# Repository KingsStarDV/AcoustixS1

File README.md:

My project AcoustixS1 is a fire extinuguisher which unlike other typical extinguisher uses SOUND WAVES to put out a flame.

Using AcoustixS1 is simple-
Turn on the toggle switch and sweep through the different frequencies using the rotary encoder.
The flame will get extinguish as you sweep through the frequencies.

I made this project as this one is unique.
I also wanted to spend my time productively.
This will also act as a line of safety for anyone who makes it.

Here is the wiring diagram-

Here is the BOM (Bill of Material)-

|Sn Number|Name|Qty|Cost|Link|
|---------|----|---|----|----|
|1|Speaker\Driver|1|950|https://www.amazon.in/FABTEC-Bass-Subwoofer-Enhanced-Low-End/dp/B0DT6CSNG8/ref=sr_1_3?crid=192DP10O75A17&dib=eyJ2IjoiMSJ9.OVpzjIeE52x4uN2hVDxxlCX0qLCRxQbtG2erD7AwG6yxwMZ7f8EWv4AVLL8WUgkA_mpQjQT_Fj_pkmhrqkyTCTO5OtNT8bGWQ8LzFvCHTCzksd2-O8yrDJKDanAHCFvzN9EQYej6w1EGBaCOx9iobEC0Yx1TN75c8lDfNnSlfrQBt9jvxze4_mL_LDm_8DIAyUvBkURTbzSwiUdASAhmS_RULj338rKEiICikLi7wDc.RIsxd0z1ZItF1Hz5PVSEdKenKYNS3Z0KPM8KLFPRmJU&dib_tag=se&keywords=fabtech%2Bsubwoofer&qid=1773637421&sprefix=FABTEC%2Caps%2C736&sr=8-3&th=1|
|2|Raspberry Pi Pico|1|390|https://robu.in/product/raspberry-pi-pico/?gad_source=1&gad_campaignid=19974686076&gbraid=0AAAAADvLFWe03Hg1PItPT--gApqtRKEj9&gclid=Cj0KCQjwsdnNBhC4ARIsAA_3hei-cacvVxjyf118IHT753eRSVcyLpk3J3DV5El-KJ_P3qYJ6TD2-goaAsIzEALw_wcB
|3|Toggle Switch|1|50|https://robu.in/product/1-month-warranty-210/?gad_source=1&gad_campaignid=17427802703&gbraid=0AAAAADvLFWcb8t9bmv2to3qo8X2Oi7sTG&gclid=Cj0KCQjwsdnNBhC4ARIsAA_3hehINwRSVwfC4ErZaWfJz_EuXLBkshijYFT9KsB1gMIg2Z3ElRRyuA8aAtuDEALw_wcB
|4|ICL7660|3|16*3|https://www.flyrobo.in/dip-icl7660scpa-icl7660-voltage-converter?tracking=ads&srsltid=AfmBOoo3MLkpT5Gyp6UgQnQZFWdhEINSU_W61YdFdvCVHnpsDx7bY_9tG_k
|5|Rotary Encoder|1|50|https://www.flyrobo.in/5v_ky-040_rotary_encoder_module_for_arduino?search=rotary%20encoder&description=true
|6|Oled Display|1|215|https://www.flyrobo.in/oled-0-96-inch-i2c-display-module?search=oled%20Display&description=true
|7|LM358|2|30*2|https://robu.in/product/lm358p-texas-instruments-operational-amplifier-2-amplifier-700-khz-0-4-v-%C2%B5s-%C2%B1-1-5v-to-%C2%B1-16v-dip-8-pins/?gad_source=1&gad_campaignid=17427802703&gbraid=0AAAAADvLFWcb8t9bmv2to3qo8X2Oi7sTG&gclid=Cj0KCQjwsdnNBhC4ARIsAA_3hejPrhMab3GLTCxWzCf_kiTKq6dgFQfSg1CrjJPDqELI7fEZG3_Ax-EaAstKEALw_wcB
|8|Amplifier Board|1|1190|https://www.amazon.in/IDUINO-Amplifier-Preamplifier-TPA3116D2-Subwoofer/dp/B0CQGHNZ58/ref=sr_1_2?crid=10M3S6SRE8RZ8&dib=eyJ2IjoiMSJ9.7YzTH9HzSaZ28NdcMxazIYrhMGw2-NO5ZobP0l6Z_-lmO61WpZXKY5r55u4-ZbThF-_HDm30yjoPGPWWFeQcBRYC57qCe6B27T9T-bv9-kq-zYKvnDsEDVWmFwKtbn54gsfz8G6lukCXoDl1qIOMAgbJtSiMkoYh9zoiSzqEPzdIRBX2cBQTi8I8C8v1p86eVMiEZ76h7d8HBHHdIEswaSX7etXxZTui9dBkM6m7TU0.gk9Pa0s7PnDQo05fv2QOO_hlsBzedNGj8SIQMNVELEk&dib_tag=se&keywords=Iduino+150W&qid=1773639446&sprefix=iduino+150%2Caps%2C380&sr=8-2
|9|18650 Samsung SDI cells|6|250*6|https://makerbazar.in/products/samsung-sdi-inr18650-li-ion-rechargeable-cells?variant=48251034140912
|10| 6S BMS|1|500|https://makerbazar.in/products/24v-6s-40a-18650-lithium-battery-protection-board?variant=43443099992304
|11| 10K Resistors|3| 10*3| local market
|12| 10nF Capcacitor|3| 15*3| local market

Total- ₹4950      ($53)

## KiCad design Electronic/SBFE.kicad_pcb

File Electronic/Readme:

in this folder, you will find pcb, 
schematics and other things related to electronics.

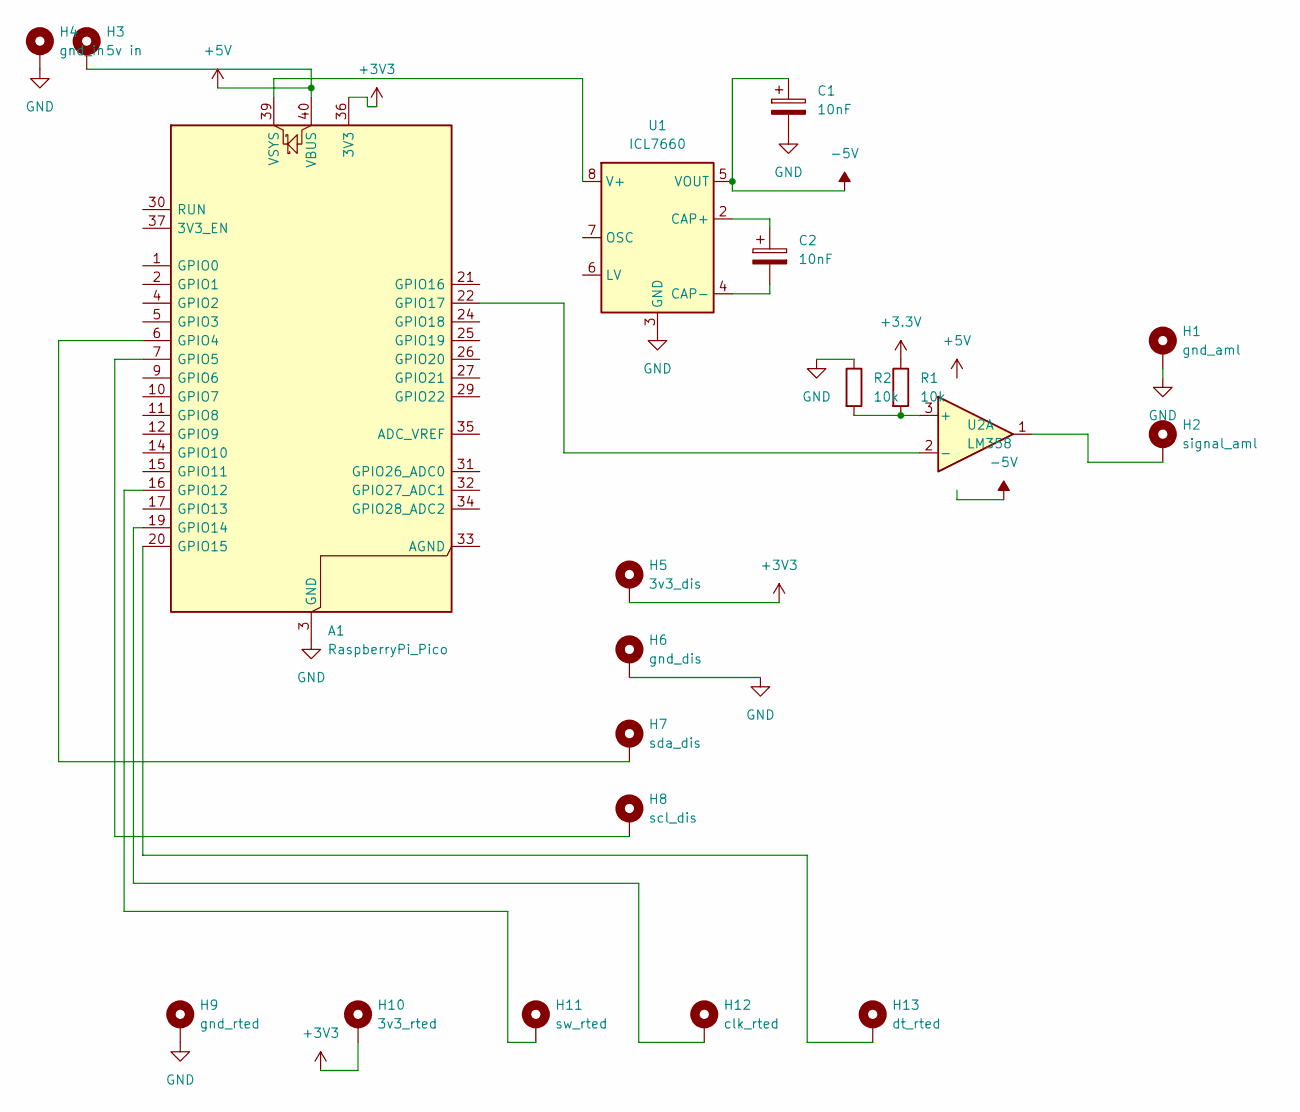
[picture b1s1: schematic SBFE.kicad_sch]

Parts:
A1: RaspberryPi_Pico; RaspberryPi_Pico_Common_Unspecified
C1, C2: 10nF; CP_Radial_D5.0mm_P2.00mm
H1: gnd_aml; MountingHole_2.2mm_M2_DIN965_Pad_TopBottom
H2: signal_aml; MountingHole_2.2mm_M2_DIN965_Pad_TopBottom
H3: 5v in; MountingHole_2.2mm_M2_DIN965_Pad_TopBottom
H4: gnd_in; MountingHole_2.2mm_M2_DIN965_Pad_TopBottom
H5: 3v3_dis; MountingHole_2.2mm_M2_DIN965_Pad_TopBottom
H6: gnd_dis; MountingHole_2.2mm_M2_DIN965_Pad_TopBottom
H7: sda_dis; MountingHole_2.2mm_M2_DIN965_Pad_TopBottom
H8: scl_dis; MountingHole_2.2mm_M2_DIN965_Pad_TopBottom
H9: gnd_rted; MountingHole_2.2mm_M2_DIN965_Pad_TopBottom
H10: 3v3_rted; MountingHole_2.2mm_M2_DIN965_Pad_TopBottom
H11: sw_rted; MountingHole_2.2mm_M2_DIN965_Pad_TopBottom
H12: clk_rted; MountingHole_2.2mm_M2_DIN965_Pad_TopBottom
H13: dt_rted; MountingHole_2.2mm_M2_DIN965_Pad_TopBottom
R1, R2: 10k; R_Axial_DIN0207_L6.3mm_D2.5mm_P7.62mm_Horizontal
U1: ICL7660; DIP-8_W7.62mm_Socket
U2: LM358; DIP-8_W7.62mm_Socket

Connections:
+3.3V: R1.1
+3V3: A1.36 (3V3), H5.1, H10.1
+5V: A1.40 (VBUS), H3.1
-5V: C1.1, U1.5 (VOUT)
GND: A1.3 (GND), A1.8 (GND), A1.13 (GND), A1.18 (GND), A1.23 (GND), A1.28 (GND), A1.38 (GND), C1.2, H1.1, H4.1, H6.1, H9.1, R2.1, U1.3 (GND)
unnamed: A1.6 (GPIO4), H7.1
unnamed: A1.7 (GPIO5), H8.1
unnamed: A1.16 (GPIO12), H11.1
unnamed: A1.19 (GPIO14), H12.1
unnamed: A1.20 (GPIO15), H13.1
unnamed: A1.22 (GPIO17), U2.2 (-)
unnamed: A1.39 (VSYS), U1.8 (V+)
unnamed: H2.1, U2.1
unnamed: C2.1, U1.2 (CAP+)
unnamed: C2.2, U1.4 (CAP-)
unnamed: R1.2, R2.2, U2.3 (+)

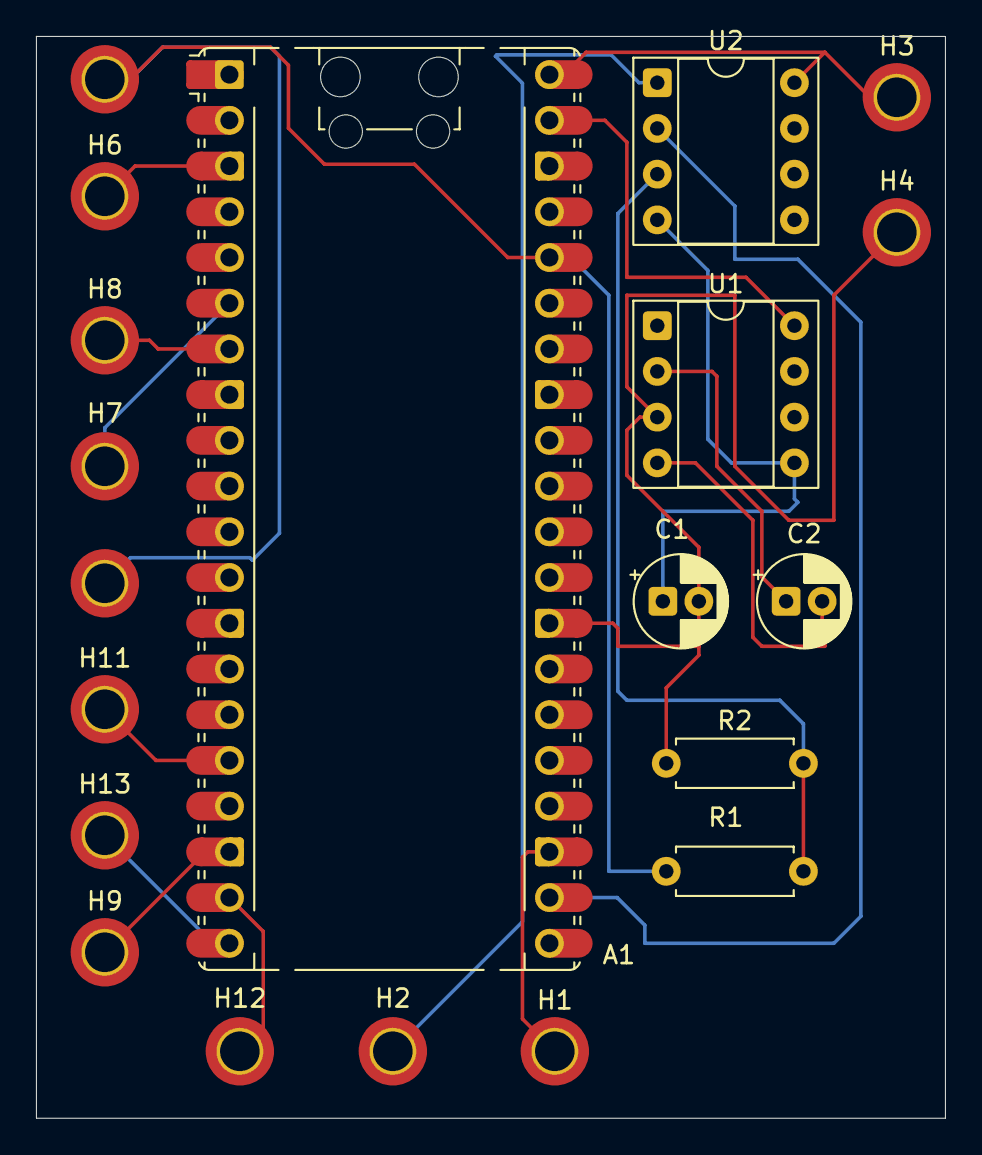
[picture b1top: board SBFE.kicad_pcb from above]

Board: 2 copper layers, 50.5 x 60.1 mm, 20 parts (0 on the bottom side), 15 nets.

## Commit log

2026-01-27 Create readme for assets
